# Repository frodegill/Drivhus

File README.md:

# Drivhus
Replacement for MiniDrivhus. This repository is for schematic for PCB and sourcecode for Arduino for a fullscale greenhouse irrigation system for up to 15 plants per Arduino

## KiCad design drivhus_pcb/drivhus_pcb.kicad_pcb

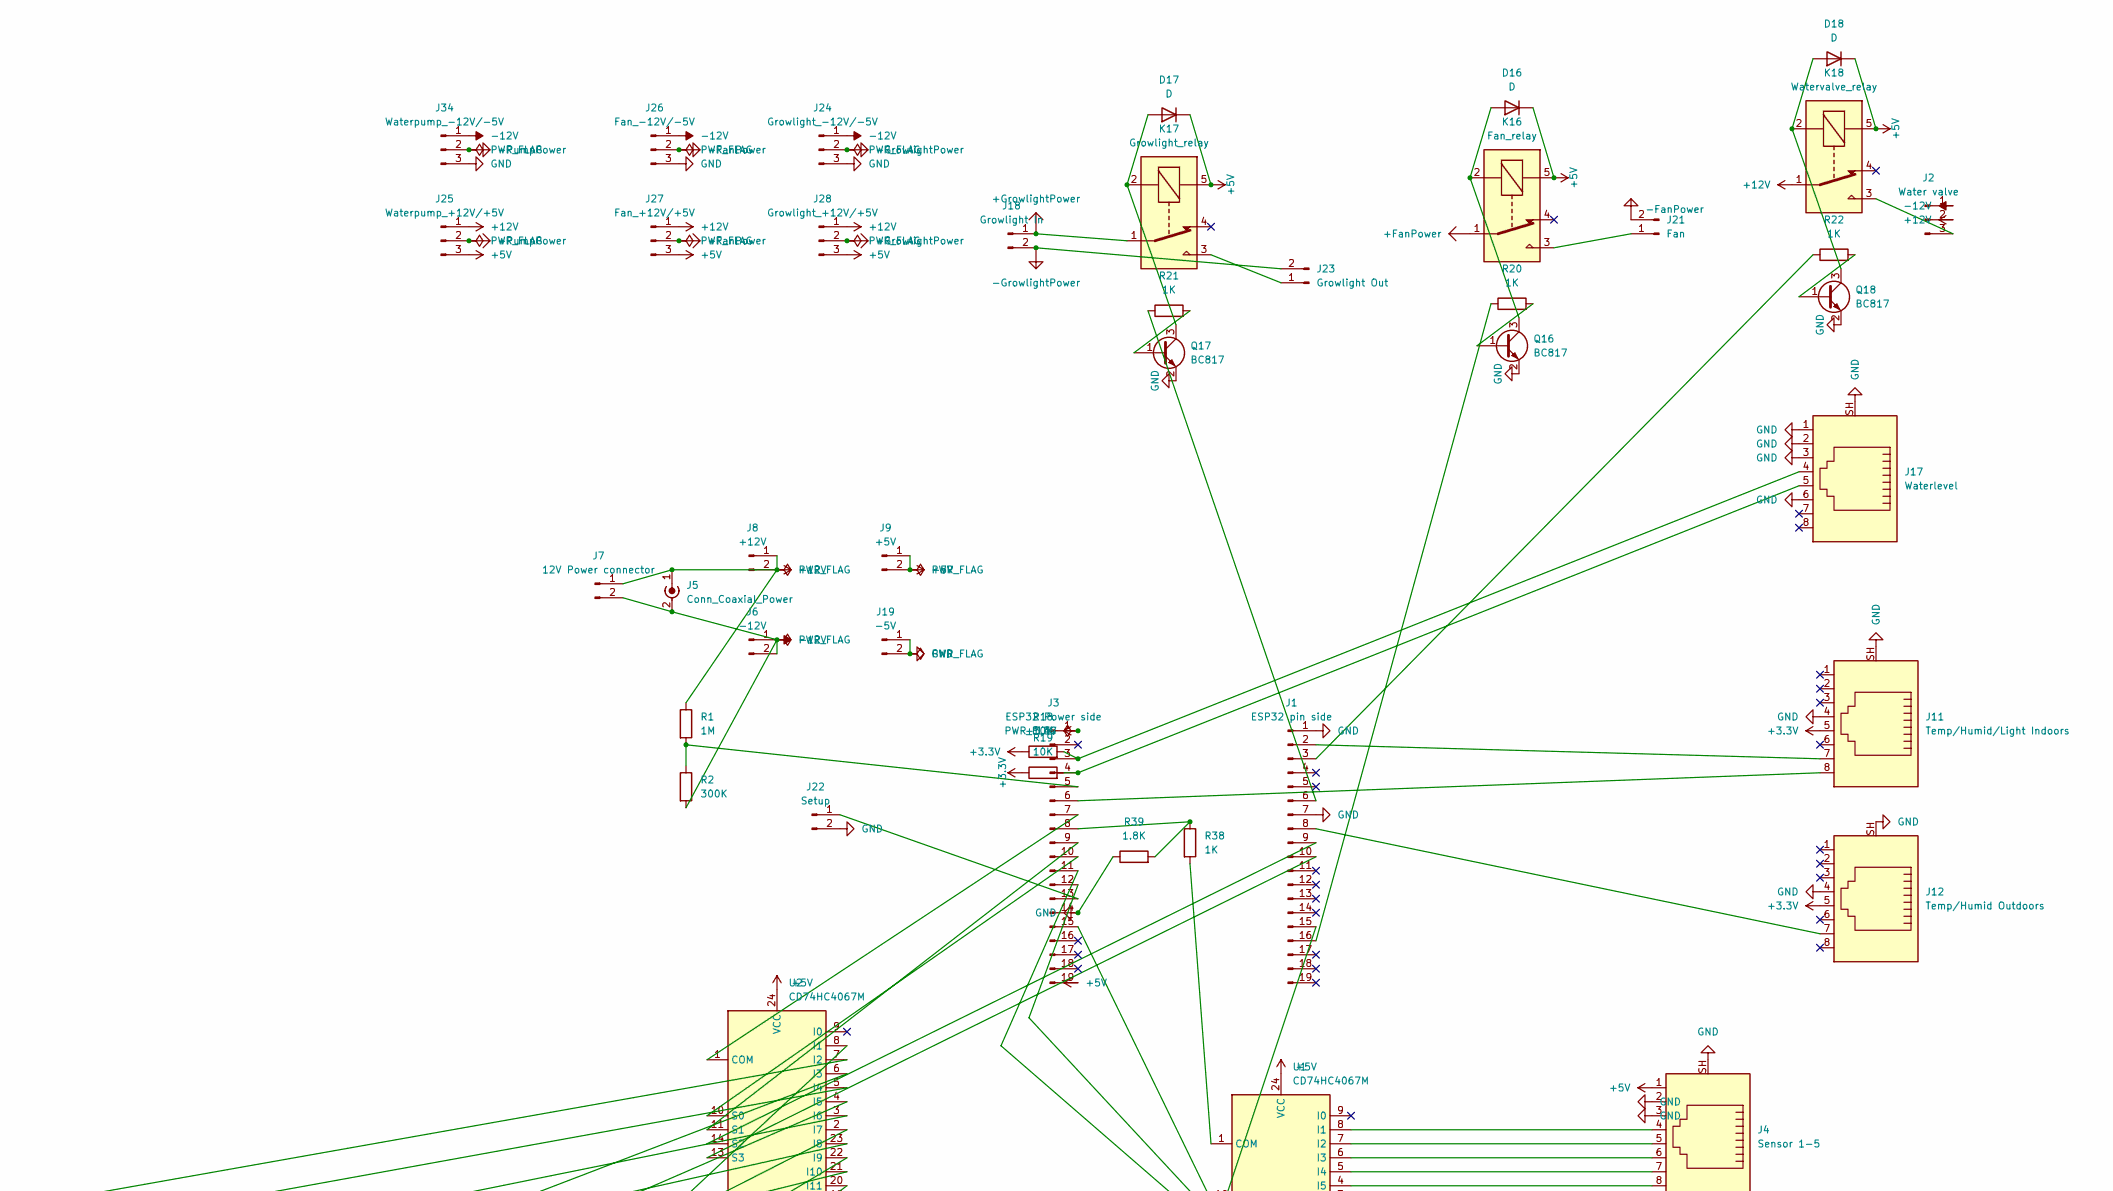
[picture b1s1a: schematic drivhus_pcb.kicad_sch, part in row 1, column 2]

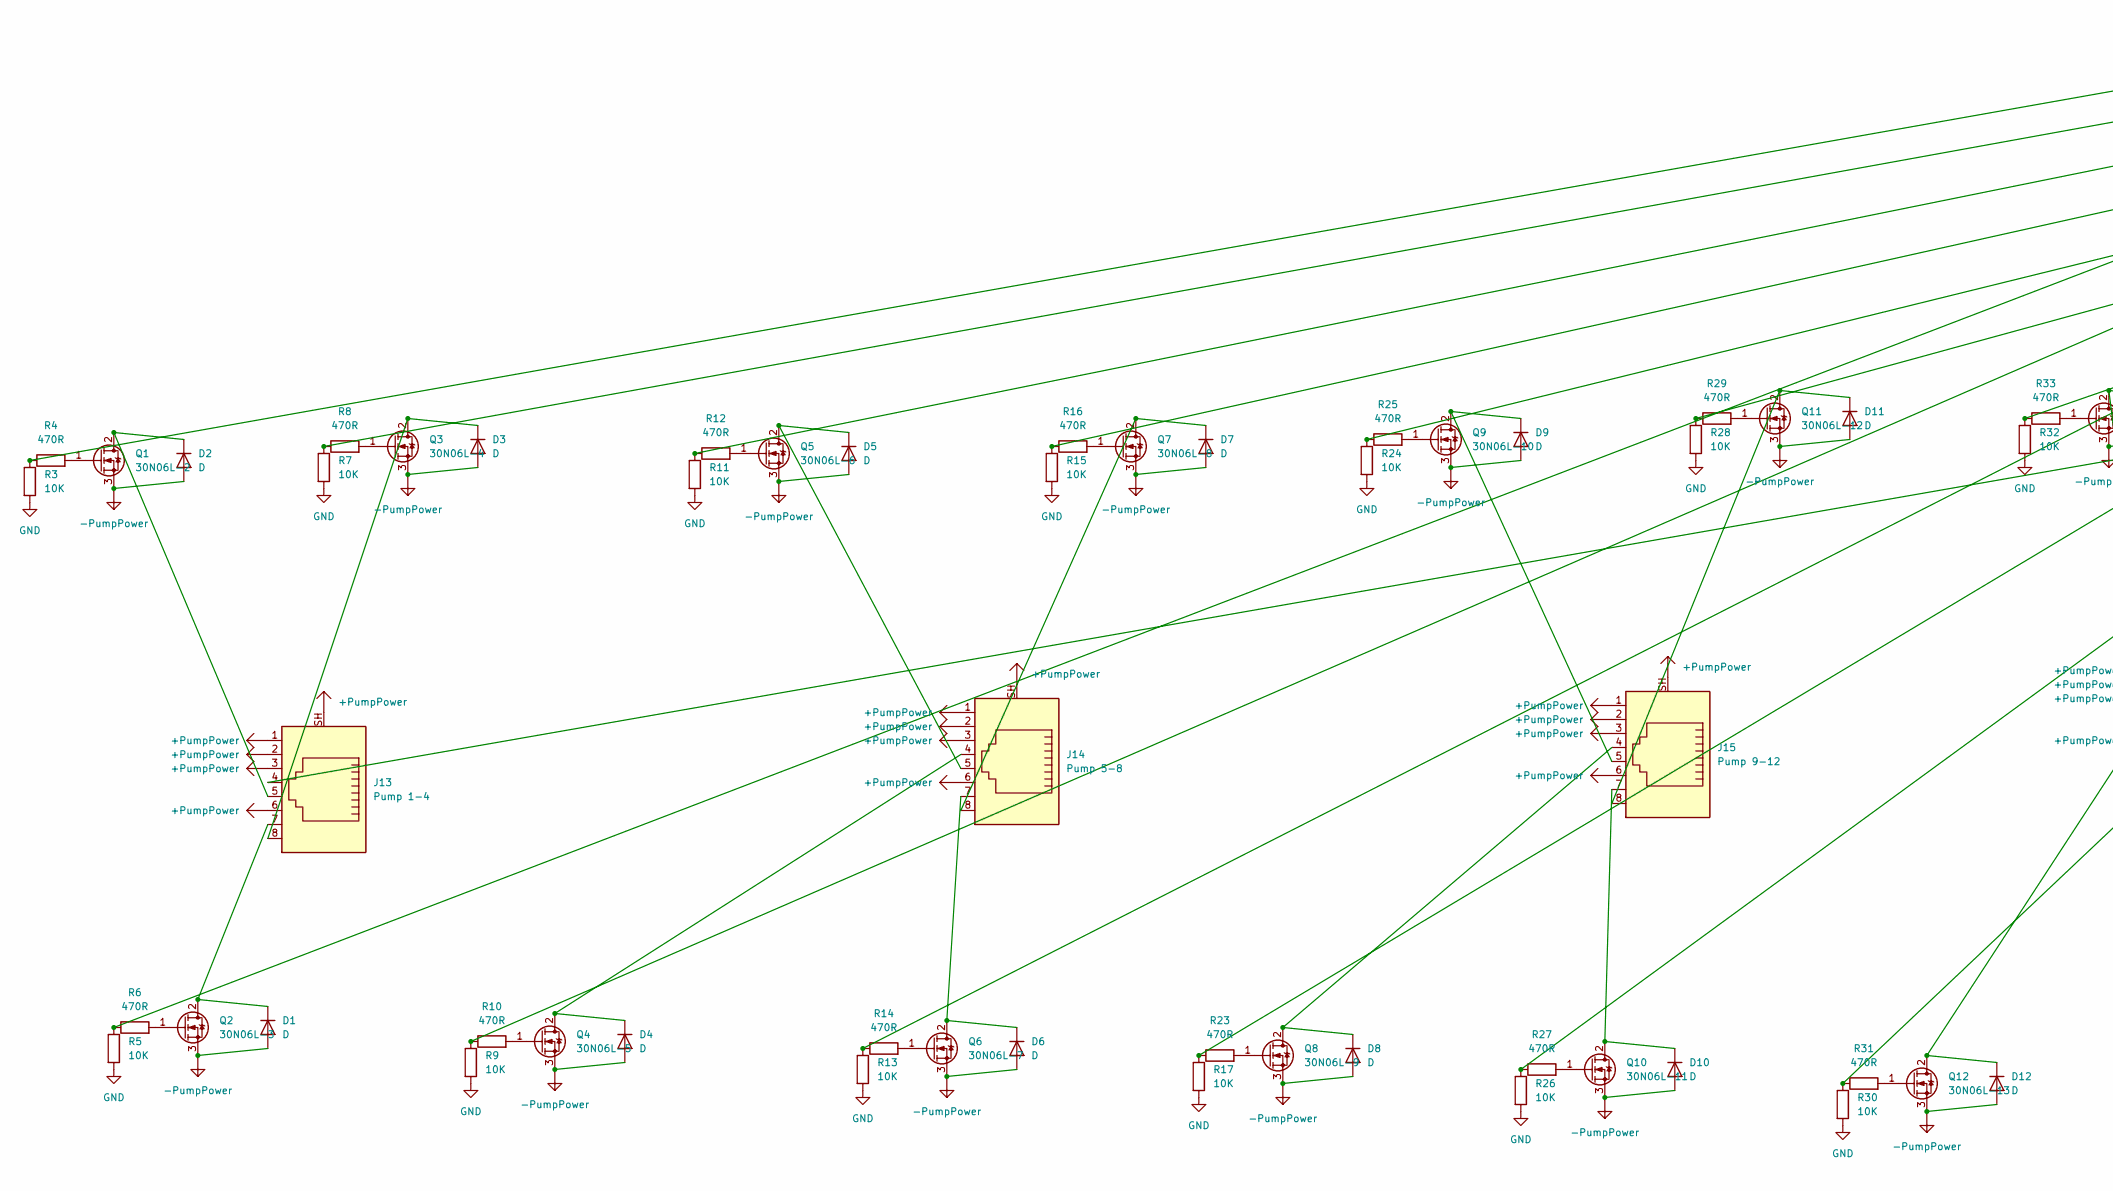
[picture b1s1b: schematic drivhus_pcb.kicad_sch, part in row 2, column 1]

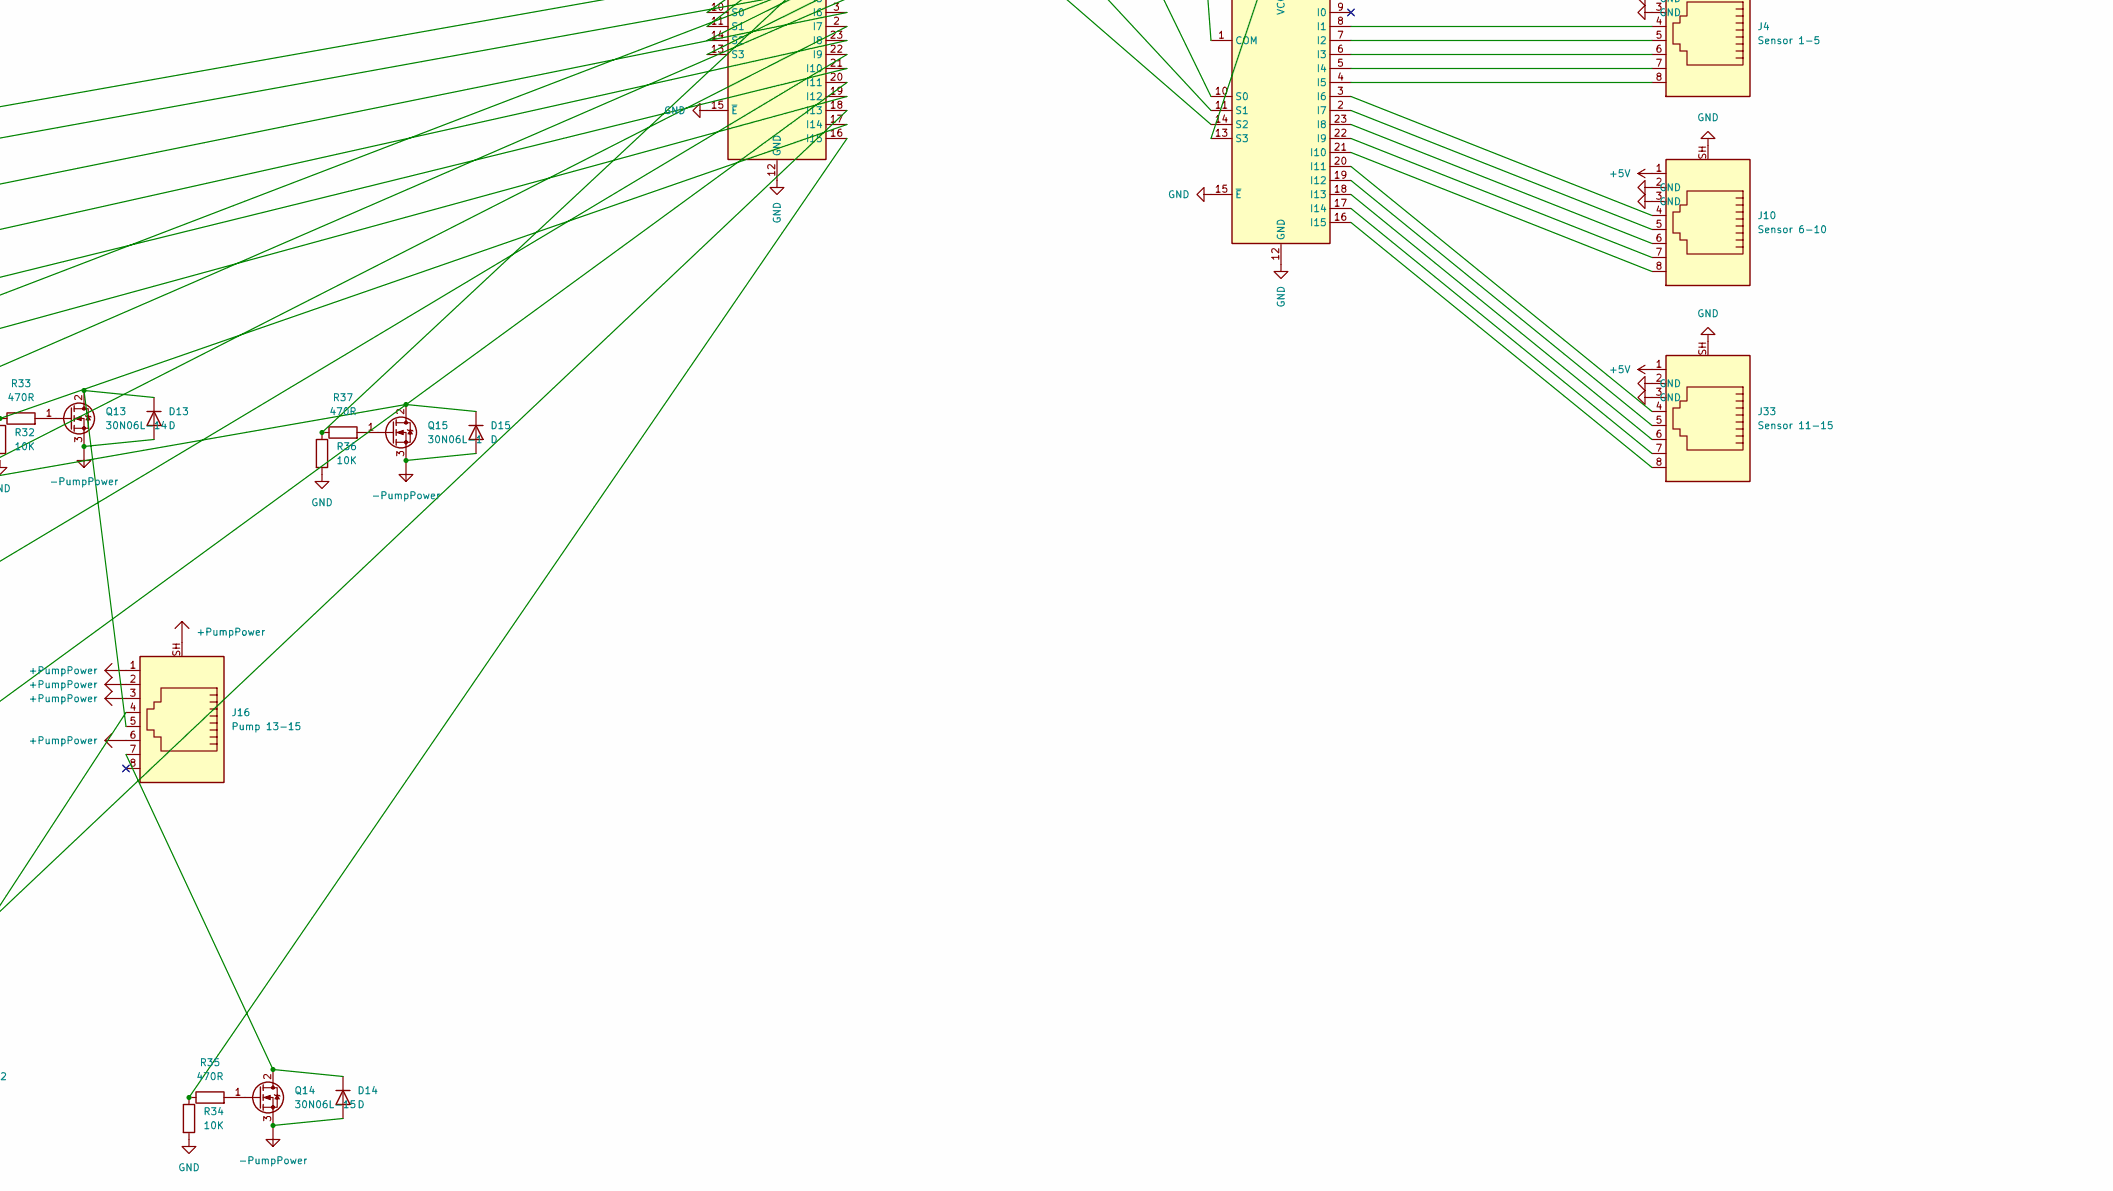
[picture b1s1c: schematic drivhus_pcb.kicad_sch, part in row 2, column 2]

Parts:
D1, D2, D3, D4, D5, D6, D7, D8, D9, D10, D11, D12, D13, D14, D15, D16, D17, D18: D; D_SMB
J1: ESP32 pin side; PinHeader_1x19_P2.54mm_Vertical
J2: Water valve; TerminalBlock_bornier-3_P5.08mm
J3: ESP32 Power side; PinHeader_1x19_P2.54mm_Vertical
J4: Sensor 1-5; RJ45_Ninigi_GE
J5: Conn_Coaxial_Power; BarrelJack_Wuerth_6941xx301002
J6: -12V; PinHeader_1x02_P2.54mm_Vertical
J7: 12V Power connector; TerminalBlock_bornier-2_P5.08mm
J8: +12V; PinHeader_1x02_P2.54mm_Vertical
J9: +5V; PinHeader_1x02_P2.54mm_Vertical
J10: Sensor 6-10; RJ45_Ninigi_GE
J11: Temp/Humid/Light Indoors; RJ45_Ninigi_GE
J12: Temp/Humid Outdoors; RJ45_Ninigi_GE
J13: Pump 1-4; RJ45_Ninigi_GE
J14: Pump 5-8; RJ45_Ninigi_GE
J15: Pump 9-12; RJ45_Ninigi_GE
J16: Pump 13-15; RJ45_Ninigi_GE
J17: Waterlevel; RJ45_Ninigi_GE
J18: Growlight In; TerminalBlock_bornier-2_P5.08mm
J19: -5V; PinHeader_1x02_P2.54mm_Vertical
J21: Fan; TerminalBlock_bornier-2_P5.08mm
J22: Setup; PinHeader_1x02_P2.54mm_Vertical
J23: Growlight Out; TerminalBlock_bornier-2_P5.08mm
J24: Growlight_-12V/-5V; PinHeader_1x03_P2.54mm_Vertical
J25: Waterpump_+12V/+5V; PinHeader_1x03_P2.54mm_Vertical
J26: Fan_-12V/-5V; PinHeader_1x03_P2.54mm_Vertical
J27: Fan_+12V/+5V; PinHeader_1x03_P2.54mm_Vertical
J28: Growlight_+12V/+5V; PinHeader_1x03_P2.54mm_Vertical
J33: Sensor 11-15; RJ45_Ninigi_GE
J34: Waterpump_-12V/-5V; PinHeader_1x03_P2.54mm_Vertical
K16: Fan_relay; Relay_SPDT_SANYOU_SRD_Series_Form_C
K17: Growlight_relay; Relay_SPDT_SANYOU_SRD_Series_Form_C
K18: Watervalve_relay; Relay_SPDT_SANYOU_SRD_Series_Form_C
Q1: 30N06L-2; TO-252-2
Q2: 30N06L-3; TO-252-2
Q3: 30N06L-4; TO-252-2
Q4: 30N06L-5; TO-252-2
Q5: 30N06L-6; TO-252-2
Q6: 30N06L-7; TO-252-2
Q7: 30N06L-8; TO-252-2
Q8: 30N06L-9; TO-252-2
Q9: 30N06L-10; TO-252-2
Q10: 30N06L-11; TO-252-2
Q11: 30N06L-12; TO-252-2
Q12: 30N06L-13; TO-252-2
Q13: 30N06L-14; TO-252-2
Q14: 30N06L-15; TO-252-2
Q15: 30N06L-1; TO-252-2
Q16, Q17, Q18: BC817; SOT-23
R1: 1M; R_1206_3216Metric
R2: 300K; R_1206_3216Metric
R3, R5, R7, R9, R11, R13, R15, R17, R18, R19, R24, R26, R28, R30, R32, R34, R36: 10K; R_1206_3216Metric
R4, R6, R8, R10, R12, R14, R16, R23, R25, R27, R29, R31, R33, R35, R37: 470R; R_1206_3216Metric
R20, R21, R22, R38: 1K; R_1206_3216Metric
R39: 1.8K; R_1206_3216Metric
U1, U2: CD74HC4067M; SOIC-24W_7.5x15.4mm_P1.27mm

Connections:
+3.3V: J3.1, J11.5, J12.5, R18.1, R19.1
+5V: D16.1 (K), D17.1 (K), D18.1 (K), J3.19, J4.1, J9.1, J9.2, J10.1, J25.3, J27.3, J28.3, J33.1, K16.5, K17.5, K18.5, U1.24 (VCC), U2.24 (VCC)
+12V: J2.2, J5.1 (In), J7.1, J8.1, J8.2, J25.1, J27.1, J28.1, K18.1, R1.1
+FanPower: J27.2, K16.1
+GrowlightPower: J18.1, J28.2, K17.1
-12V: J2.1, J5.2 (Ext), J6.1, J6.2, J7.2, J24.1, J26.1, J34.1, R2.2
-FanPower: J21.2, J26.2
-GrowlightPower: J18.2, J23.2, J24.2
-PumpPower: D1.2 (A), D2.2 (A), D3.2 (A), D4.2 (A), D5.2 (A), D6.2 (A), D7.2 (A), D8.2 (A), D9.2 (A), D10.2 (A), D11.2 (A), D12.2 (A), D13.2 (A), D14.2 (A), D15.2 (A), J34.2, Q1.3 (S), Q2.3 (S), Q3.3 (S), Q4.3 (S), Q5.3 (S), Q6.3 (S), Q7.3 (S), Q8.3 (S), Q9.3 (S), Q10.3 (S), Q11.3 (S), Q12.3 (S), Q13.3 (S), Q14.3 (S), Q15.3 (S)
unnamed: D1.1 (K), J13.7, Q2.2 (D)
unnamed: D2.1 (K), J13.5, Q1.2 (D)
unnamed: D3.1 (K), J13.8, Q3.2 (D)
unnamed: D4.1 (K), J14.4, Q4.2 (D)
unnamed: D5.1 (K), J14.5, Q5.2 (D)
unnamed: D6.1 (K), J14.7, Q6.2 (D)
unnamed: D8.1 (K), J15.4, Q8.2 (D)
unnamed: D9.1 (K), J15.5, Q9.2 (D)
unnamed: D10.1 (K), J15.7, Q10.2 (D)
unnamed: D12.1 (K), J16.4, Q12.2 (D)
unnamed: D14.1 (K), J16.7, Q14.2 (D)
unnamed: D16.2 (A), K16.2, Q16.3 (C)
unnamed: D17.2 (A), K17.2, Q17.3 (C)
unnamed: D18.2 (A), K18.2, Q18.3 (C)
unnamed: J1.2, J11.7
unnamed: J1.3, R22.1
unnamed: J1.6, R21.1
unnamed: J1.8, J12.7
unnamed: J1.9, U2.14 (S2)
unnamed: J1.10, U2.13 (S3)
unnamed: J1.15, U1.13 (S3)
unnamed: J1.16, R20.1
unnamed: J2.3, K18.3
unnamed: J3.3, J17.4, R18.2
unnamed: J3.4, J17.5, R19.2
unnamed: J3.5, R1.2, R2.1
unnamed: J3.6, J11.8
unnamed: J3.7, U2.1 (COM)
unnamed: J3.8, R38.1, R39.2
unnamed: J3.9, U2.11 (S1)
unnamed: J3.10, U2.10 (S0)
unnamed: J3.11, U1.14 (S2)
unnamed: J3.12, U1.11 (S1)
unnamed: J3.15, U1.10 (S0)
unnamed: J21.1, K16.3
unnamed: J3.13, J22.1
unnamed: J23.1, K17.3
unnamed: Q1.1 (G), R4.2
unnamed: Q2.1 (G), R6.2
unnamed: Q3.1 (G), R8.2
unnamed: Q4.1 (G), R10.2
unnamed: Q5.1 (G), R12.2
unnamed: Q6.1 (G), R14.2
unnamed: Q7.1 (G), R16.2
unnamed: Q8.1 (G), R23.2
unnamed: Q9.1 (G), R25.2
unnamed: Q10.1 (G), R27.2
unnamed: Q11.1 (G), R29.2
unnamed: Q12.1 (G), R31.2
unnamed: Q13.1 (G), R33.2
unnamed: Q14.1 (G), R35.2
unnamed: Q15.1 (G), R37.2
unnamed: Q16.1 (B), R20.2
unnamed: Q17.1 (B), R21.2
unnamed: Q18.1 (B), R22.2
unnamed: R38.2, U1.1 (COM)
unnamed: J4.4, U1.8 (I1)
unnamed: J4.5, U1.7 (I2)
unnamed: J4.6, U1.6 (I3)
unnamed: J4.7, U1.5 (I4)
unnamed: J4.8, U1.4 (I5)
unnamed: J10.4, U1.3 (I6)
unnamed: J10.5, U1.2 (I7)
unnamed: J10.6, U1.23 (I8)
unnamed: J10.7, U1.22 (I9)
unnamed: J10.8, U1.21 (I10)
unnamed: J33.4, U1.20 (I11)
unnamed: J33.5, U1.19 (I12)
unnamed: J33.6, U1.18 (I13)
unnamed: J33.7, U1.17 (I14)
unnamed: J33.8, U1.16 (I15)
unnamed: R36.1, R37.1, U2.8 (I1)
unnamed: R3.1, R4.1, U2.7 (I2)
unnamed: R7.1, R8.1, U2.5 (I4)
unnamed: R9.1, R10.1, U2.4 (I5)
unnamed: R11.1, R12.1, U2.3 (I6)
unnamed: R15.1, R16.1, U2.23 (I8)
unnamed: R17.1, R23.1, U2.22 (I9)
unnamed: R24.1, R25.1, U2.21 (I10)
unnamed: R30.1, R31.1, U2.18 (I13)
unnamed: R34.1, R35.1, U2.16 (I15)

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
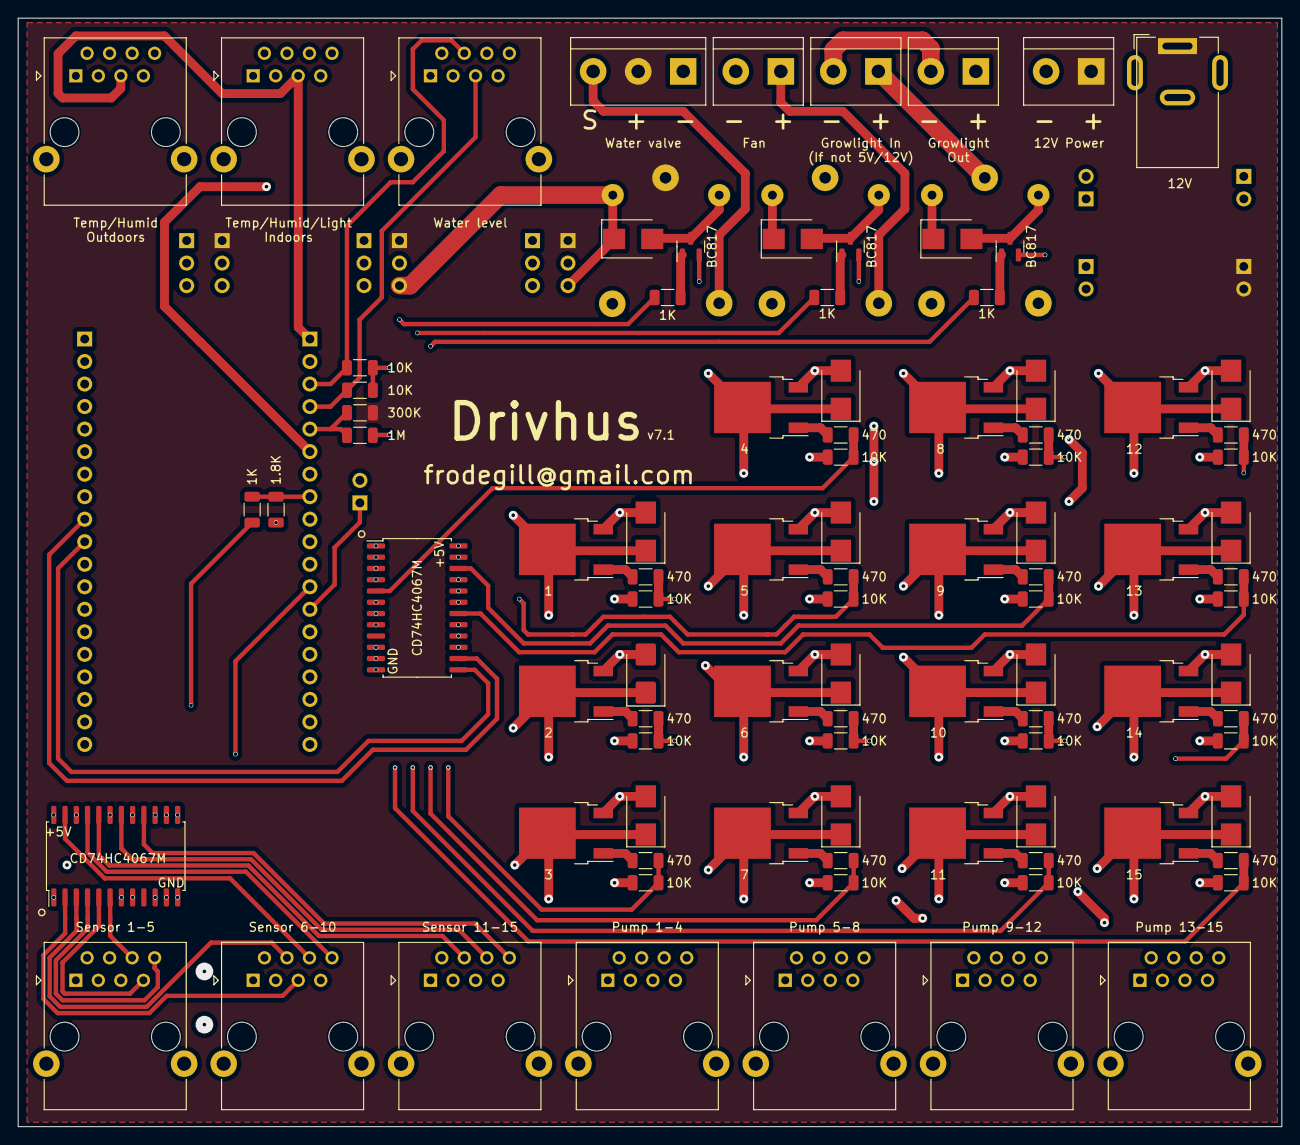
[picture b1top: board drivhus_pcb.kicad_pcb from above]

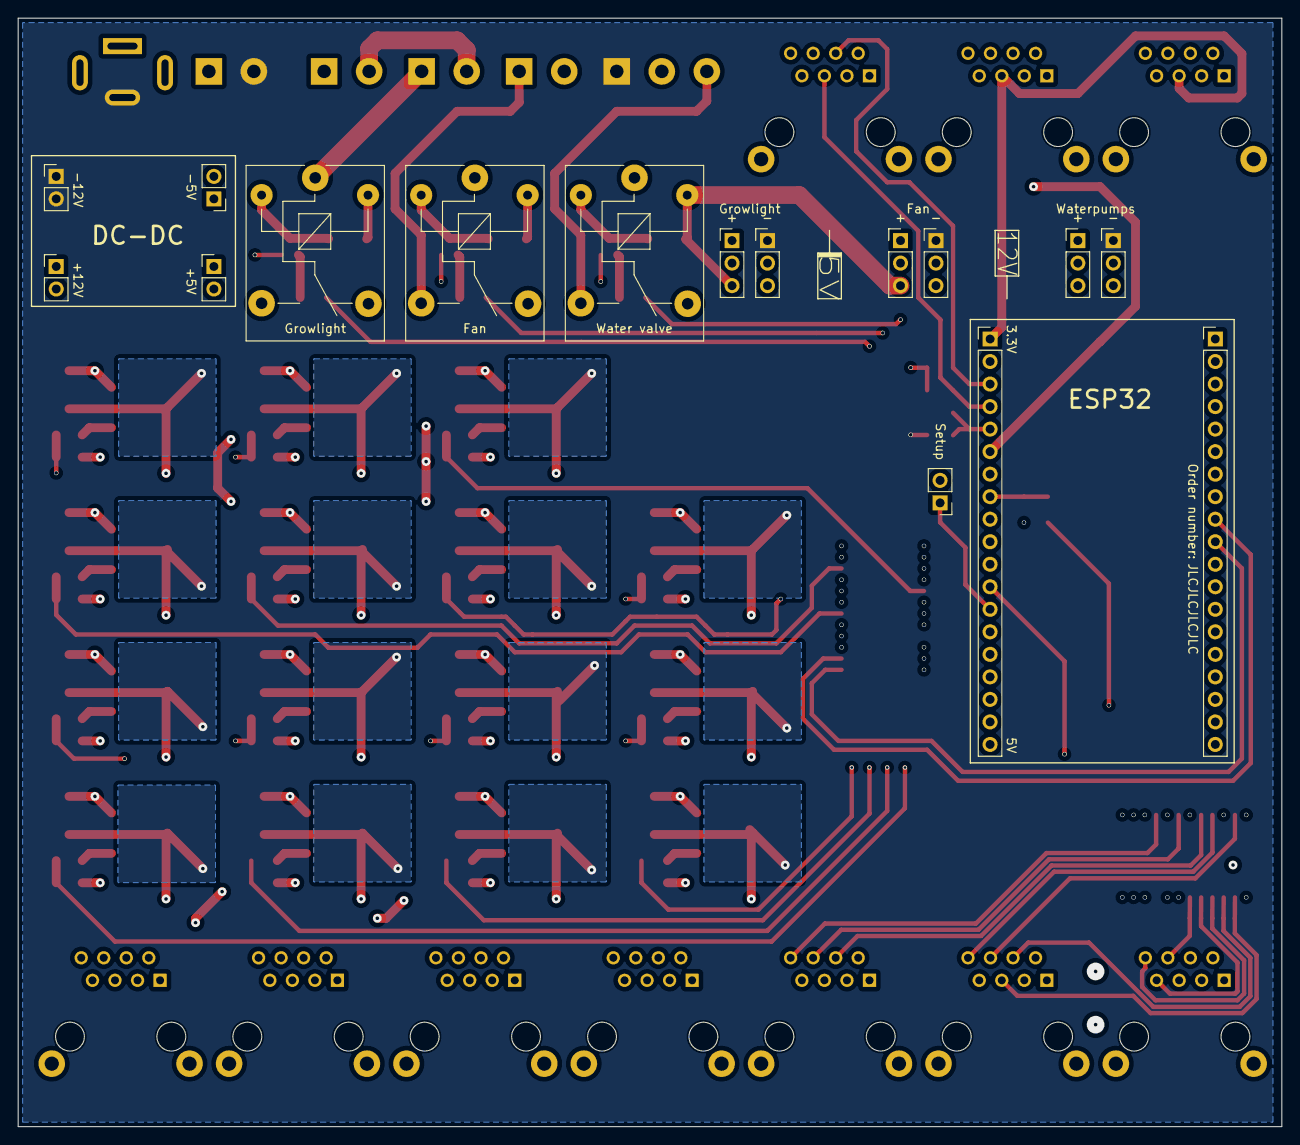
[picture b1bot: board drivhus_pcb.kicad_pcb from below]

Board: 4 copper layers, 142.5 x 125.0 mm, 109 parts (16 on the bottom side), 101 nets.

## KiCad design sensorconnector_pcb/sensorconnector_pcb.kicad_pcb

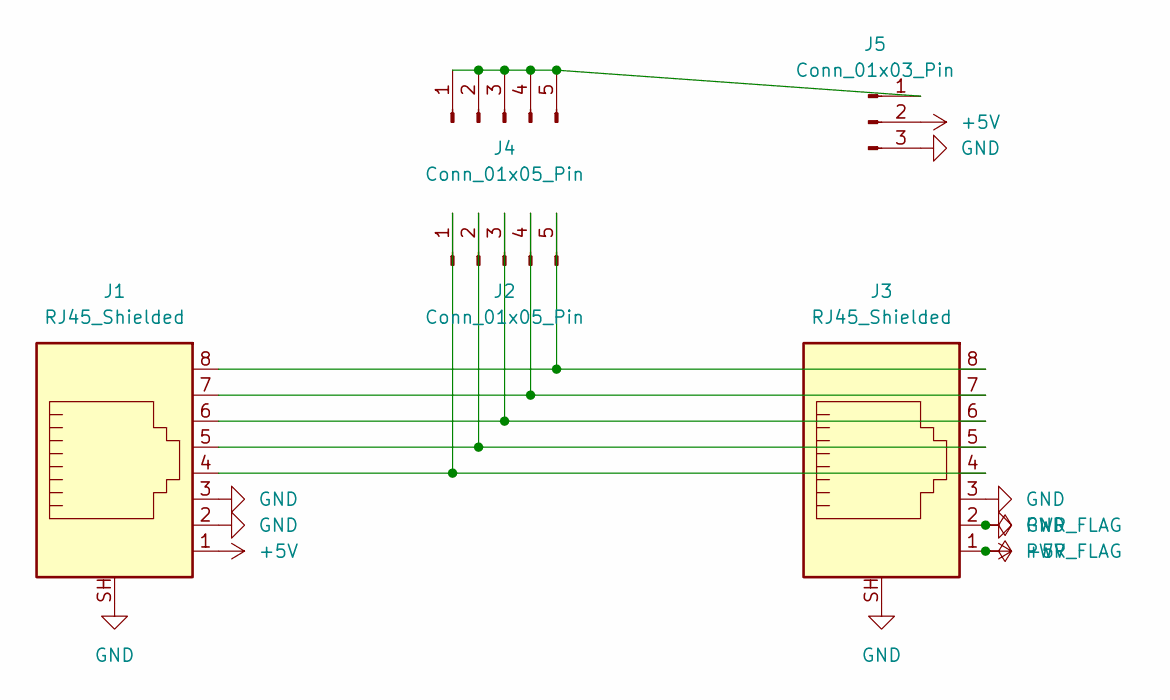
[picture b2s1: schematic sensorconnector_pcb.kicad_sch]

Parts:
J1, J3: RJ45_Shielded; RJ45_Ninigi_GE
J2, J4: Conn_01x05_Pin; PinHeader_1x05_P2.54mm_Vertical
J5: Conn_01x03_Pin; TerminalBlock_bornier-3_P5.08mm

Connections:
+5V: J1.1, J3.1, J5.2
GND: J1.2, J1.3, J1.SH, J3.2, J3.3, J3.SH, J5.3
unnamed: J1.4, J2.1, J3.4
unnamed: J1.5, J2.2, J3.5
unnamed: J1.6, J2.3, J3.6
unnamed: J1.7, J2.4, J3.7
unnamed: J1.8, J2.5, J3.8
unnamed: J4.1, J4.2, J4.3, J4.4, J4.5, J5.1

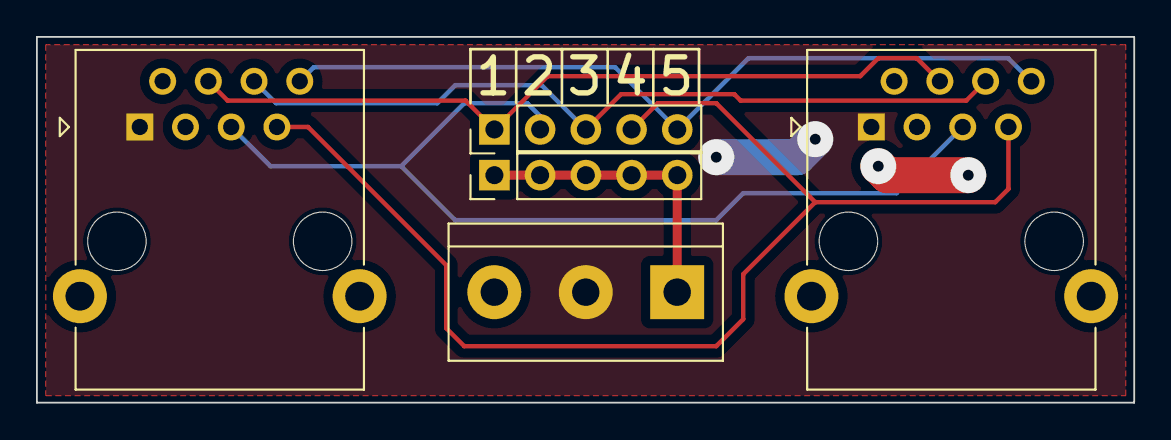
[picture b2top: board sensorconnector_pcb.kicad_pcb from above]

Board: 2 copper layers, 61.0 x 20.3 mm, 5 parts (0 on the bottom side), 8 nets.

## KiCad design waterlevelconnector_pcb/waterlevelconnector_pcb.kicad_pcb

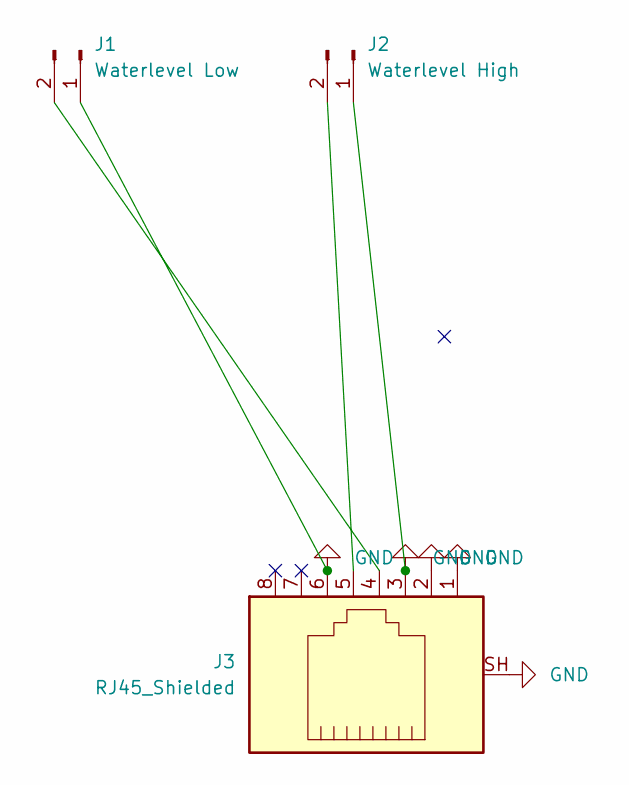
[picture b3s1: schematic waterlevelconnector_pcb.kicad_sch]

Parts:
J1: Waterlevel Low; TerminalBlock_bornier-2_P5.08mm
J2: Waterlevel High; TerminalBlock_bornier-2_P5.08mm
J3: RJ45_Shielded; RJ45_Ninigi_GE

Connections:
GND: J1.1, J2.1, J3.1, J3.2, J3.3, J3.6, J3.SH
unnamed: J1.2, J3.4
unnamed: J2.2, J3.5

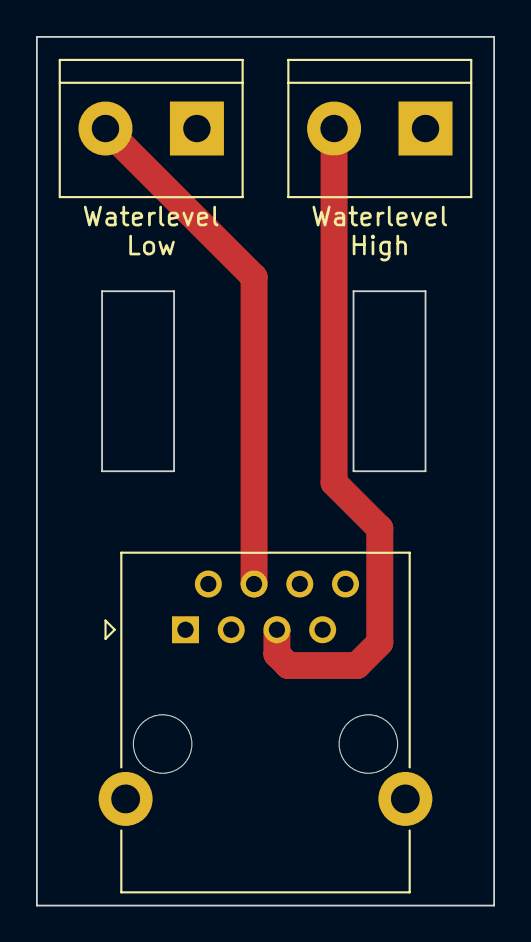
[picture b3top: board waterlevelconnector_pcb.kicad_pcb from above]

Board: 2 copper layers, 25.4 x 48.3 mm, 3 parts (0 on the bottom side), 3 nets.

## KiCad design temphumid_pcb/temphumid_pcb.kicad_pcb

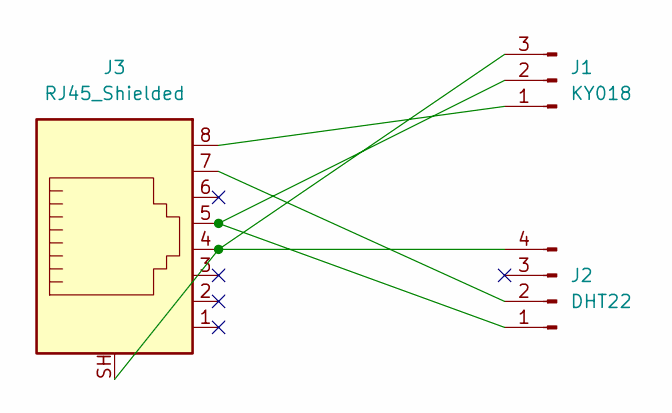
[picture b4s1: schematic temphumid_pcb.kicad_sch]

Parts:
J1: KY018; PinHeader_1x03_P2.00mm_Vertical
J2: DHT22; AM2302
J3: RJ45_Shielded; RJ45_Ninigi_GE

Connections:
unnamed: J1.3, J2.4, J3.4, J3.SH
unnamed: J1.2, J2.1, J3.5
unnamed: J2.2, J3.7
unnamed: J1.1, J3.8

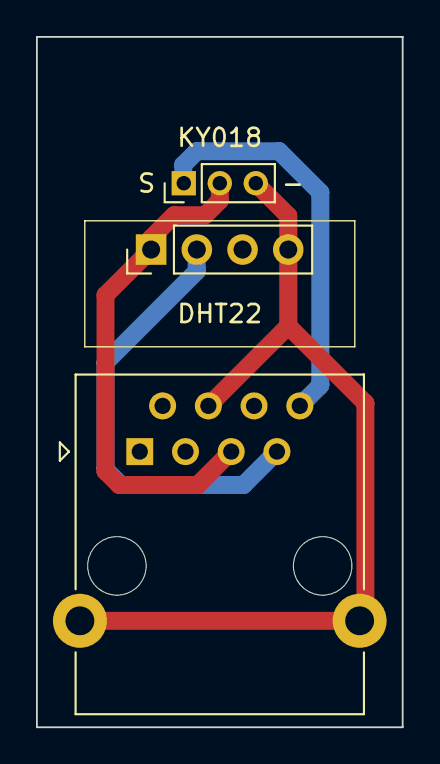
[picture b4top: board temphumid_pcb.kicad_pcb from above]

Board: 2 copper layers, 20.3 x 38.4 mm, 3 parts (0 on the bottom side), 4 nets.

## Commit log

2023-11-04 Added schematics for MAX485
2023-11-05 WEbServer with WebSocket for RS485. Work In Progress, based on modbus example
2023-11-09 More WebServer WIP
2023-11-10 More WebServer work
2023-11-15 Added stup mode jumper to schematics
2023-11-16 Added pins for the DC-DC power
2023-11-18 Added PCB for sensor connector
2023-11-18 Use RJ45 as quick-connect for RS-485 bus. Two connectors, so controller can be in the middle of bus
2023-11-23 Added voltage sensor (max 14.5V)
2023-11-26 Lots of webserver WIP
2023-11-28 Added code for DHT22 and KY018
2023-11-28 Added connectors for indoor and outdoor temp/humid/light sensors
2023-11-28 Added PCB for temp/humid/light sensor
2023-11-29 Added updating temp,humidity,light and voltage
2023-11-29 Added support for custom Volt multiplier
2023-11-30 Do not activate WiFi STA mode if no SSID is set
2023-12-01 Added some KiCAD gitignores
2023-12-01 Added relays. Added lots and lots of relays...
2023-12-01 Cleaned up the schematic power lines
2023-12-03 Added connector for pumps
2023-12-05 WIP cd74hc4067 support (for waterpumps)
2023-12-07 Added NTP support
2023-12-08 Added schematics and PCB for waterlevel switches
2023-12-08 Added pins for waterlevel switches
2023-12-10 Removed unused includes
2023-12-10 Added support for waterlevel low/high sensors and water valve
2023-12-12 Renamed to explicitly tell if pins are Input or Output
2023-12-13 Added remaining parts and connections to schematics
2023-12-15 Finished the Drivhus PCB design
2023-12-20 Make it possible to compile with up-to-date desktop compiler for improved compiler warnings
2023-12-29 Added more compiler warnings
2024-01-07 Added explicit namespace. Also added UI for relay test and placeholder for GPIO Viewer
2024-01-10 Made cd74hc4067 more self-aware, and aded initial support for fan and growlight. Test Relay should work now
2024-01-16 Too many changes, so a WIP commit. Started on emulating growlight location and onChange listeners
2024-01-21 Lots of growlight time related changes. Also changed to more specific listeners, and fixed nasty bug in EEPROM handling of max length strings
2024-01-22 Remuved unneeded whitespace
2024-01-22 Turn growlight on/off based on sunrise/sunset
2024-01-22 Fan and Growlight are logically identical
2024-01-22 Volt and Light sensor are logically identical
2024-02-09 More MQTT work in progress
2024-02-09 Make a common Component class
2024-02-09 Resolved a ToDo
2024-02-13 Added component name
2024-02-13 Default Serial to 115200 baud
2024-02-14 Implemented plant watering and some refactoring
2024-02-15 Implemented humidity support for fan
2024-02-15 Cache fan configs
2024-02-16 Prepare for config change listener
2024-02-16 Do not return some values for disabled plants
2024-02-16 Settings should be master for values
2024-02-21 Show calculated outdoor as indoor humidity. Also some sensor scan refactoring
2024-02-21 Function should return value
2024-02-23 Mark direction of SP3485EN
2024-05-16 Some minor changes
2024-05-16 Actual implementation of water level triggers and -valve
2024-05-16 Added small project to set RS484 address to stubborn sensors
2024-05-19 Do not water if bucket is empty or plant is disabled
2024-05-19 Clear sensor value when disabeling plant
2024-05-19 Show plant watering range, and handle NAN as humidity better
2024-05-22 Make webserver into a separate component
2024-05-22 Started working on MQTT. Still WIP
2024-05-25 Do not process MQTT in disconnected state
2024-05-25 Use notification system for setup mode change
2024-06-05 Use Log wrapper for Serial messages
2024-06-05 Prevent use before init
2024-06-07 Split plants and other fields in enum, clean up lots of MQTT
2024-06-07 Removed extra SUNSET field, and made plants changed into 16-bit (there are only 15 plants)
2024-06-08 Actually implemented logging over MQTT
2024-06-24 Lots of small fixes
2024-06-25 Use JSON also for config
2024-06-25 Added fan active status
2024-06-26 Prepare for release logging
2024-06-26 Do not log IP over MQTT before MQTT connection is requested
2024-06-26 Fixed off-by-one error and made switch types more explicit
2024-07-03 Fixed problems found while compiling with a more up-to-date compiler
2024-10-21 Changed to multiplexed analog sensors and MOSFETs
2025-01-17 Updated to a multiplexed analog humidity sensor connector
2025-01-17 New revision of main irrigation system PCB
2025-03-03 Major rewrite of webserver because of switching back to analog sensors and running out of space on ESP32
2025-03-13 Web UI enable/disable sensor
2025-03-18 Cannot use ADC2 together with WiFi on ESP32
2025-04-20 Fixed disabled active sensor handling
2025-04-21 Send outside-as-inside humidity to MQTT
2025-04-21 moisture:0% should be dry, moisture:100% should be wet
2025-04-21 extend water valve open time
